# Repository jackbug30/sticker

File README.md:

# Sticker Stock Ticker

This is a stock ticker (built completely from scratch). Using 40 red/green 8x8 LED modules, custom PCBs, and an ESP32, it can display stock prices and changes.

By its nature of displaying test, it doesn't necessarily need to be a stock ticker. It could be used as a general text display (such as a clock).

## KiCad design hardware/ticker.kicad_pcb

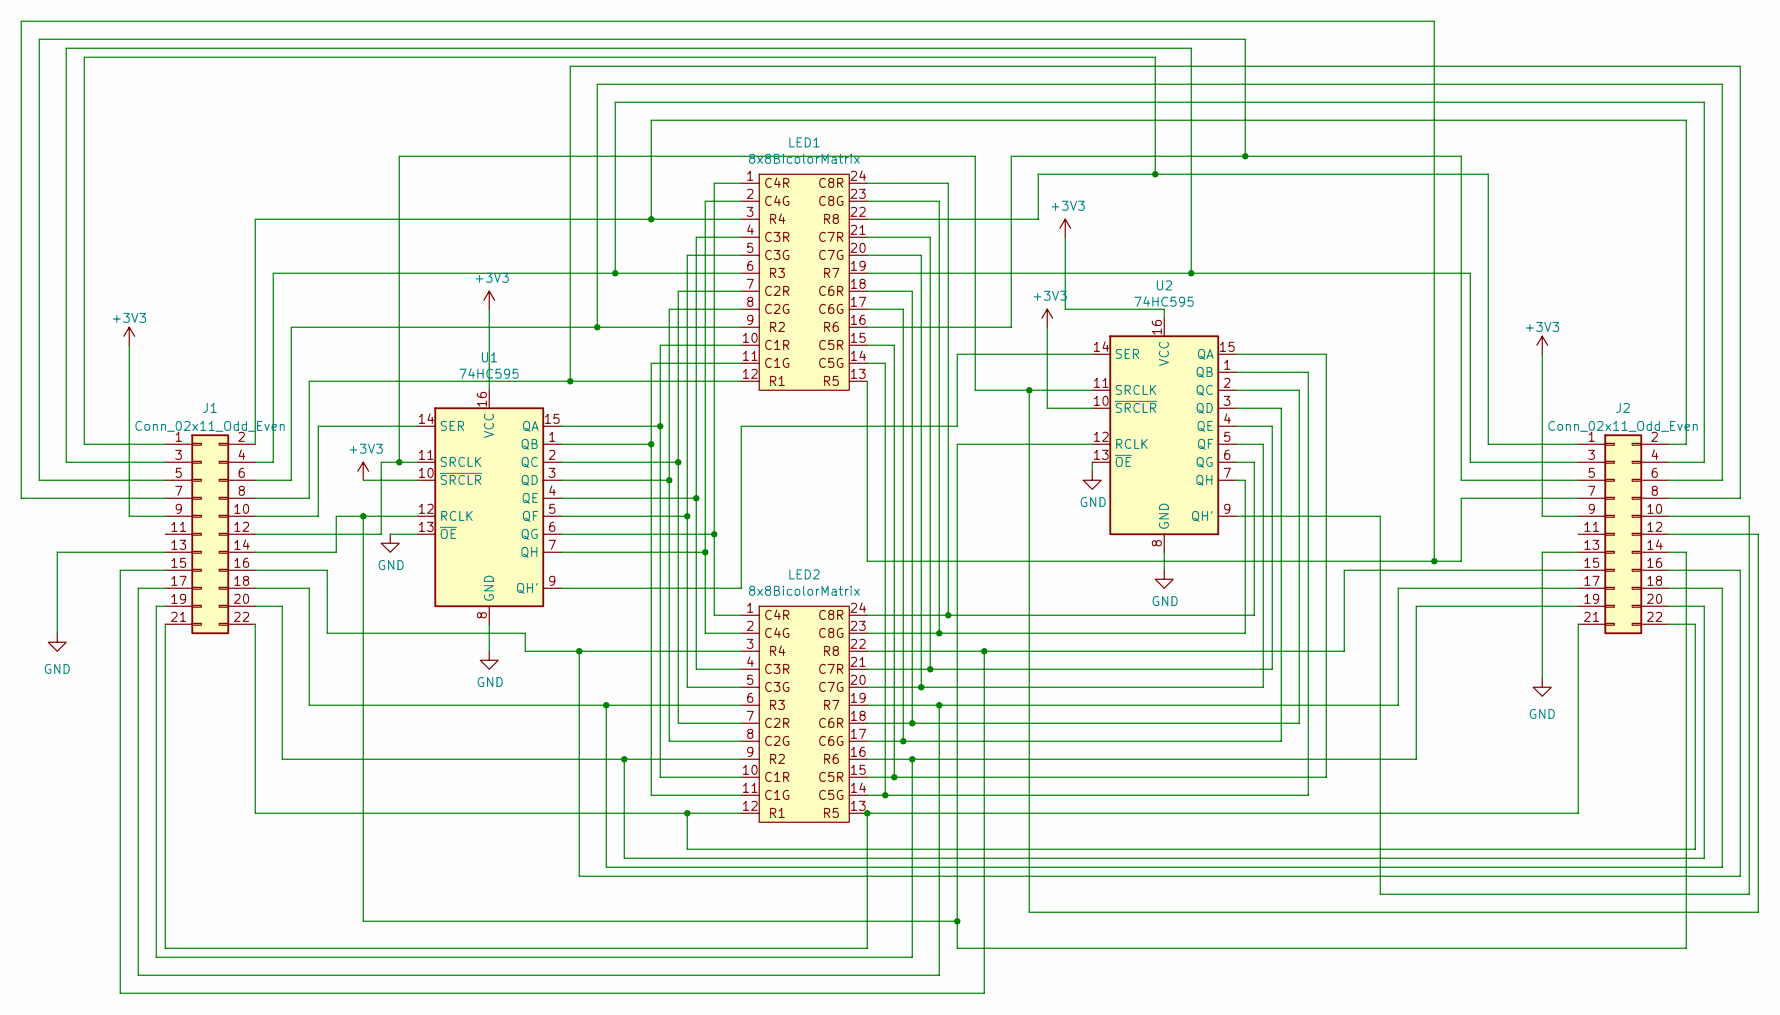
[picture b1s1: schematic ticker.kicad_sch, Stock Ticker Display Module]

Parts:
J1, J2: Conn_02x11_Odd_Even; PinHeader_2x11_P2.54mm_Vertical
LED1, LED2: 8x8BicolorMatrix
U1, U2: 74HC595; DIP-16_W7.62mm_LongPads

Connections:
+3V3: J1.9, J2.9, U1.10 (~SRCLR), U1.16 (VCC), U2.10 (~SRCLR), U2.16 (VCC)
GND: J1.13, J2.13, U1.8 (GND), U1.13 (~OE), U2.8 (GND), U2.13 (~OE)
unnamed: J1.1, J2.1, LED1.22
unnamed: J1.2, J2.2, LED1.3
unnamed: J1.3, J2.3, LED1.19
unnamed: J1.4, J2.4, LED1.6
unnamed: J1.5, J2.5, LED1.16
unnamed: J1.6, J2.6, LED1.9
unnamed: J1.7, J2.7, LED1.13
unnamed: J1.8, J2.8, LED1.12
unnamed: J1.10, U1.14 (SER)
unnamed: J1.12, J2.12, U1.11 (SRCLK), U2.11 (SRCLK)
unnamed: J1.14, J2.14, U1.12 (RCLK), U2.12 (RCLK)
unnamed: J1.15, J2.15, LED2.22
unnamed: J1.16, J2.16, LED2.3
unnamed: J1.17, J2.17, LED2.19
unnamed: J1.18, J2.18, LED2.6
unnamed: J1.19, J2.19, LED2.16
unnamed: J1.20, J2.20, LED2.9
unnamed: J1.21, J2.21, LED2.13
unnamed: J1.22, J2.22, LED2.12
unnamed: J2.10, U2.9 (QH')
unnamed: LED1.10, LED2.10, U1.15 (QA)
unnamed: LED1.11, LED2.11, U1.1 (QB)
unnamed: LED1.7, LED2.7, U1.2 (QC)
unnamed: LED1.8, LED2.8, U1.3 (QD)
unnamed: LED1.4, LED2.4, U1.4 (QE)
unnamed: LED1.5, LED2.5, U1.5 (QF)
unnamed: LED1.1, LED2.1, U1.6 (QG)
unnamed: U1.9 (QH'), U2.14 (SER)
unnamed: LED1.2, LED2.2, U1.7 (QH)
unnamed: LED1.15, LED2.15, U2.15 (QA)
unnamed: LED1.14, LED2.14, U2.1 (QB)
unnamed: LED1.18, LED2.18, U2.2 (QC)
unnamed: LED1.17, LED2.17, U2.3 (QD)
unnamed: LED1.21, LED2.21, U2.4 (QE)
unnamed: LED1.20, LED2.20, U2.5 (QF)
unnamed: LED1.24, LED2.24, U2.6 (QG)
unnamed: LED1.23, LED2.23, U2.7 (QH)

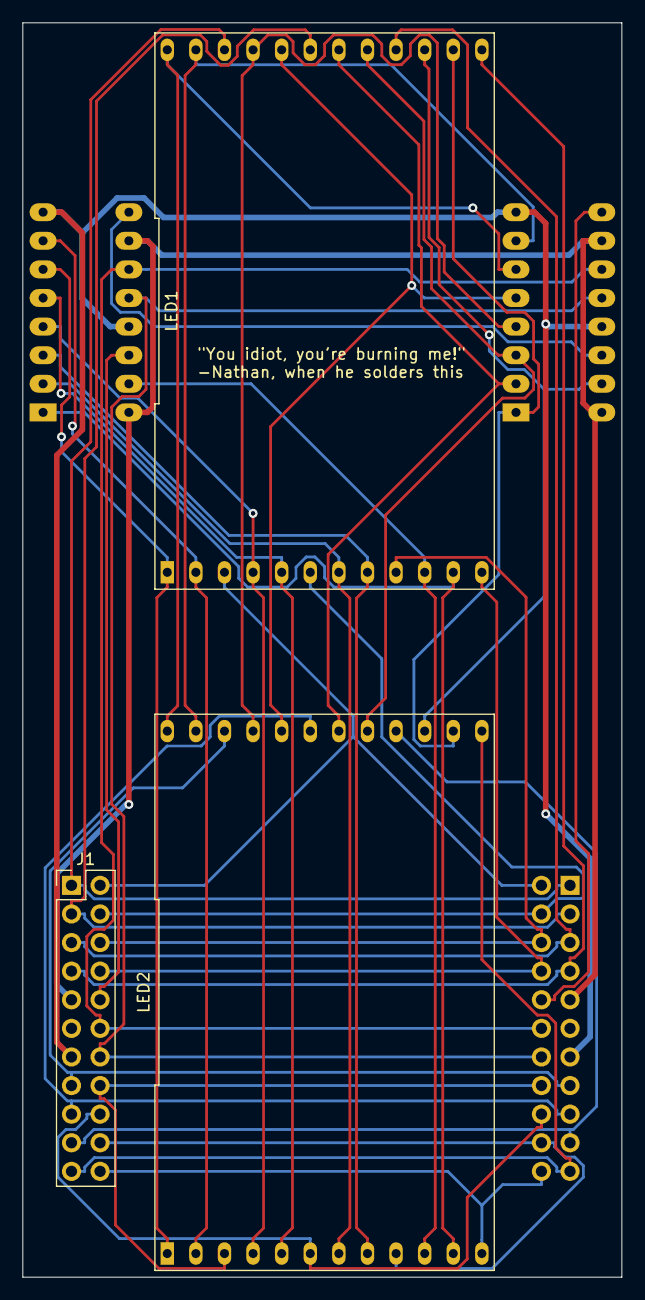
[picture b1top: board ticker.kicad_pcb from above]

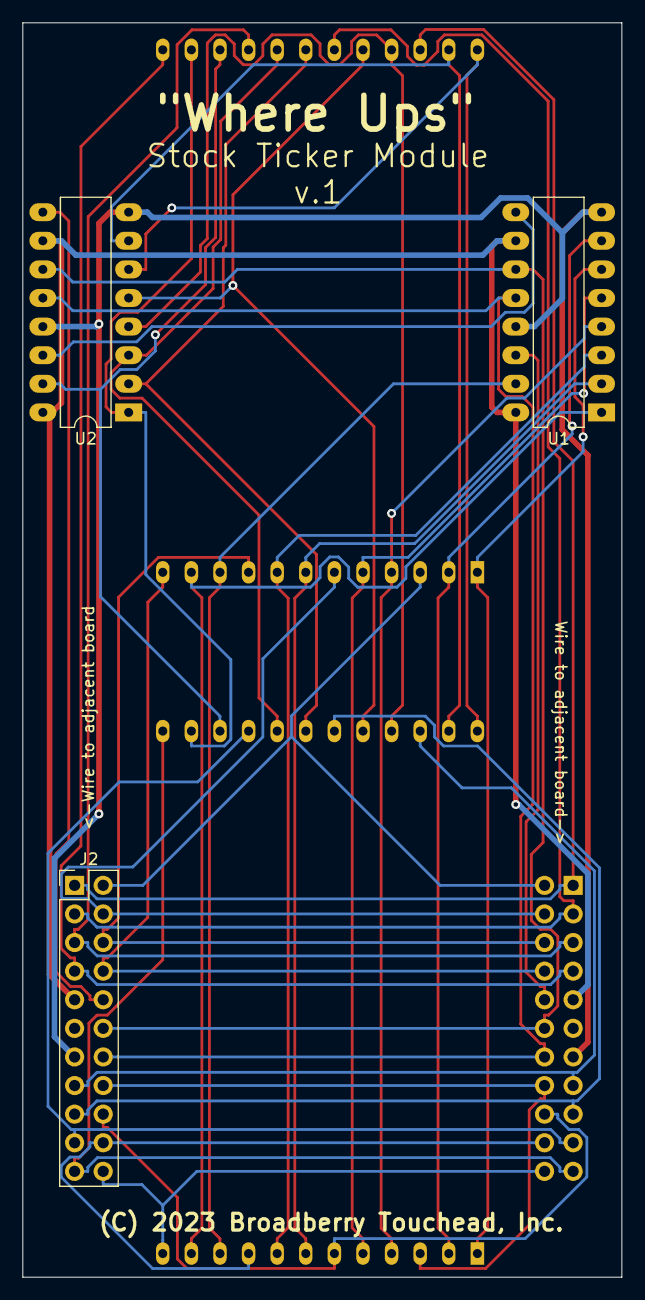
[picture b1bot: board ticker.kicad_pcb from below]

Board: 2 copper layers, 53.2 x 111.4 mm, 6 parts (3 on the bottom side), 39 nets.

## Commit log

2023-04-10 Initial
    Put hw and sw folders into repo
2023-04-10 Updated font importing
2023-04-10 test by adding test line
2023-04-10 Revert "test by adding test line"
    This reverts commit 5bc7b37dd193e4fe943ed4150200b19d464c9e23.

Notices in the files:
hardware/ticker.kicad_pcb:
(C) 2023 Broadberry Touchead, Inc.
